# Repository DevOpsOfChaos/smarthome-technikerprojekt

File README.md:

# smarthome-technikerprojekt

Smart-Home-Grundsystem – Technikerarbeit 2026

## Projektübersicht

Eigenständig entwickeltes, lokal betriebenes Smart-Home-Grundsystem mit selbst aufgebauten Mikrocontrollergeräten, ESP-NOW-Funkkommunikation und Node-RED-Dashboard.

- **Keine Cloud** – alles läuft lokal
- **Keine Herstellerbindung** – ESP32-C3, eigene Platinen, eigene Firmware
- **Vollständig nachvollziehbar** – von der Platine bis zur Bedienoberfläche

## Architektur

```
Geräte (ESP32-C3) ──ESP-NOW──▶ Master ──MQTT──▶ Server (Raspberry Pi)
                                                 ├── Mosquitto (Broker)
                                                 ├── Node-RED (Logik + Dashboard)
                                                 └── SQLite (Persistenz)
```

## Gerätetypen

| Typ | Instanzen | Funktion |
|-----|-----------|----------|
| **net_erl** | Hall-Light, Kitchen | Relais, Umweltsensorik, Bewegung |
| **net_zrl** | Rollladen | 2-Relais-Steuerung, Kalibrierung |
| **net_sen** | Außensensor | BME280, VEML7700, Regensensor |
| **bat_sen** | Regen, Fenster | Batteriebetrieb, Deep-Sleep |

## Repository-Struktur

| Verzeichnis | Inhalt |
|-------------|--------|
| `firmware/` | **Hauptbestandteil** – PlatformIO-Projekt mit Basistypen und konkreten Geräteinstanzen |
| `hardware/` | KiCAD-Schaltpläne, Platinenlayouts, 3D-Modelle |
| `server/` | Docker-Compose-Stack (Mosquitto, Node-RED, SQLite) |
| `docs/` | Technische Dokumentation und Referenz |
| `tests/` | Testskripte und Checklisten |
| `PROTOKOLL/` | Entwicklungs- und Testprotokolle (Nachweise) |
| `esphome/` | ESPHome-Alternativlinie (nicht Bestandteil der Technikerarbeit) |

## Zwei Firmware-Linien

### Eigene Firmware (Hauptlinie)
Die eigene C++-Firmware unter `firmware/` ist der Kern des Technikerprojekts. Sie nutzt:
- **Basistyp-Architektur** – wiederverwendbare Runtime-Klassen (`NetErlRuntime`, `NetSenRuntime`, etc.)
- **ESP-NOW** – direkte Funkkommunikation zwischen Geräten und Master
- **Master-Bridge** – Übersetzung zwischen ESP-NOW und MQTT
- **Vollständige Kontrolle** – Timing, Provisionierung, Fehlerbehandlung in eigenem Code

### ESPHome-Alternative
Unter `esphome/` liegt eine alternative MQTT-Linie für Nutzer, die ESPHome oder Home Assistant bevorzugen. Diese Geräte sprechen direkt MQTT mit demselben Serververtrag. Die ESPHome-Linie ist nicht Bestandteil der Technikerarbeit, sondern eine praktische Erweiterung für Anwender.

## Quick Start

### Server starten
```bash
cd server
docker compose up -d
```
Dashboard: http://localhost:1880/ui

### Firmware bauen
```bash
cd firmware
pio run -e net_erl_hall_light -t upload
```

## Technologien

- **MCU:** ESP32-C3 (RISC-V)
- **Kommunikation:** ESP-NOW (lokal), MQTT (Server)
- **Server:** Node-RED, Mosquitto, SQLite, Docker
- **Firmware:** PlatformIO, Arduino-Framework
- **Hardware:** KiCAD, Eigenentwurf

## Lizenz

All rights reserved. Dieses Repository ist Teil einer schulischen Prüfungsleistung.  
Nach Abschluss der Prüfung behält sich der Autor einen Wechsel auf eine freizügigere Lizenz vor.

## Autor

Manuel Ries – Heinrich-Hertz-Schule Karlsruhe – Technikerarbeit 2026

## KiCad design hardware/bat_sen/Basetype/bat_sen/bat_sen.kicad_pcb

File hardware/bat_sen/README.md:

# BAT-SEN — Batteriebetriebener Sensor-Knoten (Basetype)

> `device_class: bat_sen` | `SH_CLASS_BAT_SEN (0x04)`

## Übersicht

BAT-SEN ist der Basetype für **batteriebetriebene Sensor-Knoten** mit Deep-Sleep. Optimiert für minimale Ruhestromaufnahme.

## KiCAD-Quellen

👉 **[kicad/](kicad/)** — Vollständiges KiCAD-Projekt

| Datei | Beschreibung |
|-------|-------------|
| `bat_sen.kicad_pro` | Projektdatei |
| `bat_sen.kicad_sch` | Root-Schaltplan (hierarchisch) |
| `Leistungskreis.kicad_sch` | Sub-Sheet: Power-Gating, Batterie |
| `Steuerstromkreis.kicad_sch` | Sub-Sheet: ESP32 + I²C |
| `bat_sen.kicad_pcb` | PCB-Layout (2-Lagen) |
| `Pinbelegung/Pinbelegung.txt` | GPIO-Belegung |
| `Code/SamplecodeBasis.txt` | ESP-NOW Deep-Sleep Beispiel |
| `production/` | BOM, Position, Netlist |

### SVG-Schaltpläne

- [schematics/bat_sen.svg](schematics/bat_sen.svg) — Root
- [schematics/bat_sen-Leistungskreis.svg](schematics/bat_sen-Leistungskreis.svg) — Power-Gating
- [schematics/bat_sen-Steuerstromkreis.svg](schematics/bat_sen-Steuerstromkreis.svg) — ESP32

## Stromspar-Design

- **Power-Gating:** P-MOSFET (IRF9530, SOT-23) schaltet Sensoren im Deep-Sleep ab
- **Zener-Diode:** BZX55C3V3 (DO-35) — Überspannungsschutz
- **Spannungsteiler:** R2+R5 (100K+100K) an GPIO4 — Batterieüberwachung
- **Deep-Sleep:** ~0.5–0.8 mA Board-Gesamtstrom
- **Wake-Up:** Timer (RTC) oder externer Interrupt

## Pinbelegung (Basetype)

| GPIO | Funktion | Bemerkung |
|------|----------|-----------|
| GPIO0 | I²C SDA | Optional |
| GPIO1 | I²C SCL | Optional |
| GPIO2 | Setup-Button | Lokaler Setup-/Bring-up-Taster |
| GPIO4 | V-Mess (ADC) | Batteriespannung via Spannungsteiler |
| GPIO3–10 | frei | Pinheader |
| GPIO20/21 | UART | Debug |

## Batterie-Profile

| Profil | Typ | Spannung | Kapazität |
|--------|-----|----------|-----------|
| `BAT_PROFILE_CR2032` | CR2032 | 3.0V | ~225 mAh |
| `BAT_PROFILE_2X_AA` | 2× AA | 3.0V | ~2500 mAh |
| `BAT_PROFILE_2X_AAA` | 2× AAA | 3.0V | ~1000 mAh |

## Geräte (Devices)

| Gerät | ID | Sensoren | Batterie |
|-------|-----|----------|----------|
| 👉 [bat_sen_01](devices/bat_sen_01_window_contact/) | Fensterkontakt | Reed-Schalter | 2x AAA in Serie |
| 👉 [bat_sen_02](devices/bat_sen_02_rain_sensor/) | Regensensor | ADC-Regensensor | 2× AA |

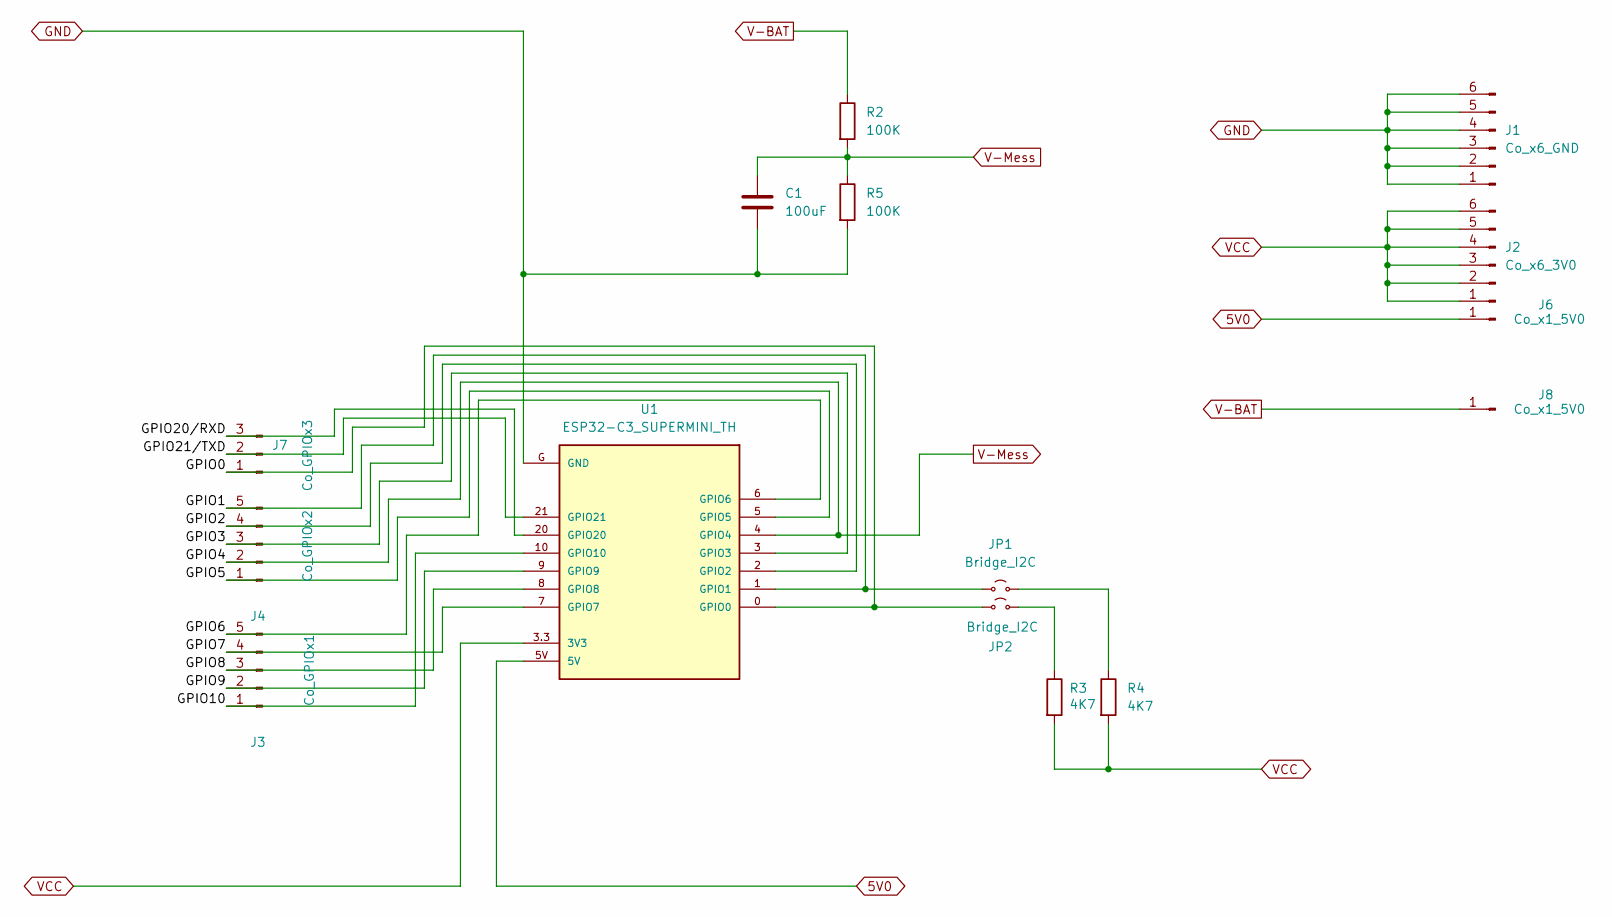
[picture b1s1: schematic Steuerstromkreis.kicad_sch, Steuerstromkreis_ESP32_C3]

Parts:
C1: 100uF; C_0603_1608Metric_Pad1.08x0.95mm_HandSolder
J1: Co_x6_GND; PinHeader_1x06_P2.54mm_Vertical
J2: Co_x6_3V0; PinHeader_1x06_P2.54mm_Vertical
J3: Co_GPIOx1; PinHeader_1x05_P2.54mm_Vertical
J4: Co_GPIOx2; PinHeader_1x05_P2.54mm_Vertical
J6, J8: Co_x1_5V0; PinHeader_1x01_P2.54mm_Vertical
J7: Co_GPIOx3; PinHeader_1x03_P2.54mm_Vertical
JP1, JP2: Bridge_I2C; SolderJumper-2_P1.3mm_Open_Pad1.0x1.5mm
R2, R5: 100K; R_0603_1608Metric_Pad0.98x0.95mm_HandSolder
R3, R4: 4K7; R_0805_2012Metric_Pad1.20x1.40mm_HandSolder
U1: ESP32-C3_SUPERMINI_TH; MODULE_ESP32-C3_SUPERMINI_TH

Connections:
5V0: J6.1, U1.5V
/Steuerstromkreis/GPIO0: J7.1, JP2.1 (A), U1.0 (GPIO0)
/Steuerstromkreis/GPIO1: J4.5, JP1.1 (A), U1.1 (GPIO1)
/Steuerstromkreis/GPIO2: J4.4, U1.2 (GPIO2)
/Steuerstromkreis/GPIO3: J4.3, U1.3 (GPIO3)
/Steuerstromkreis/GPIO5: J4.1, U1.5 (GPIO5)
/Steuerstromkreis/GPIO6: J3.5, U1.6 (GPIO6)
/Steuerstromkreis/GPIO7: J3.4, U1.7 (GPIO7)
/Steuerstromkreis/GPIO8: J3.3, U1.8 (GPIO8)
/Steuerstromkreis/GPIO9: J3.2, U1.9 (GPIO9)
/Steuerstromkreis/GPIO10: J3.1, U1.10 (GPIO10)
/Steuerstromkreis/GPIO20/RXD: J7.3, U1.20 (GPIO20)
/Steuerstromkreis/GPIO21/TXD: J7.2, U1.21 (GPIO21)
GND: C1.1, J1.1, J1.2, J1.3, J1.4, J1.5, J1.6, R5.2, U1.G (GND); also elsewhere on the board
unnamed: JP1.2 (B), R4.1
unnamed: JP2.2 (B), R3.1
V-BAT: J8.1, R2.1
V-Mess: C1.2, J4.2, R2.2, R5.1, U1.4 (GPIO4)
VCC: J2.1, J2.2, J2.3, J2.4, J2.5, J2.6, R3.2, R4.2, U1.3.3 (3V3); also elsewhere on the board

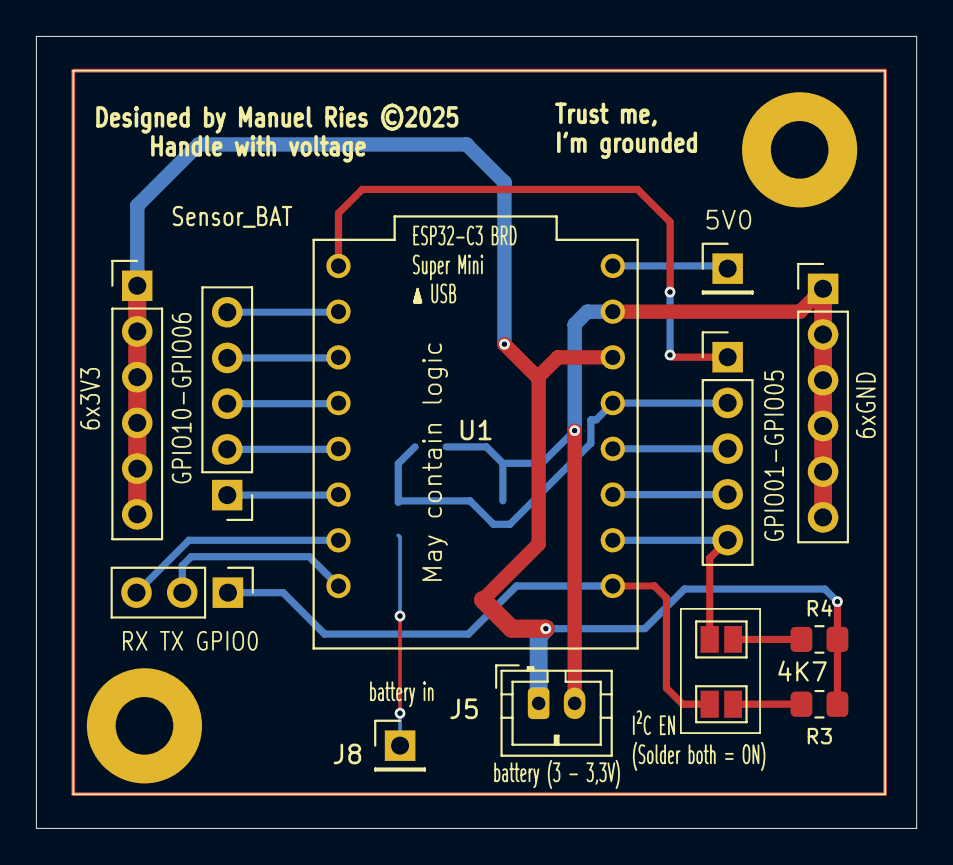
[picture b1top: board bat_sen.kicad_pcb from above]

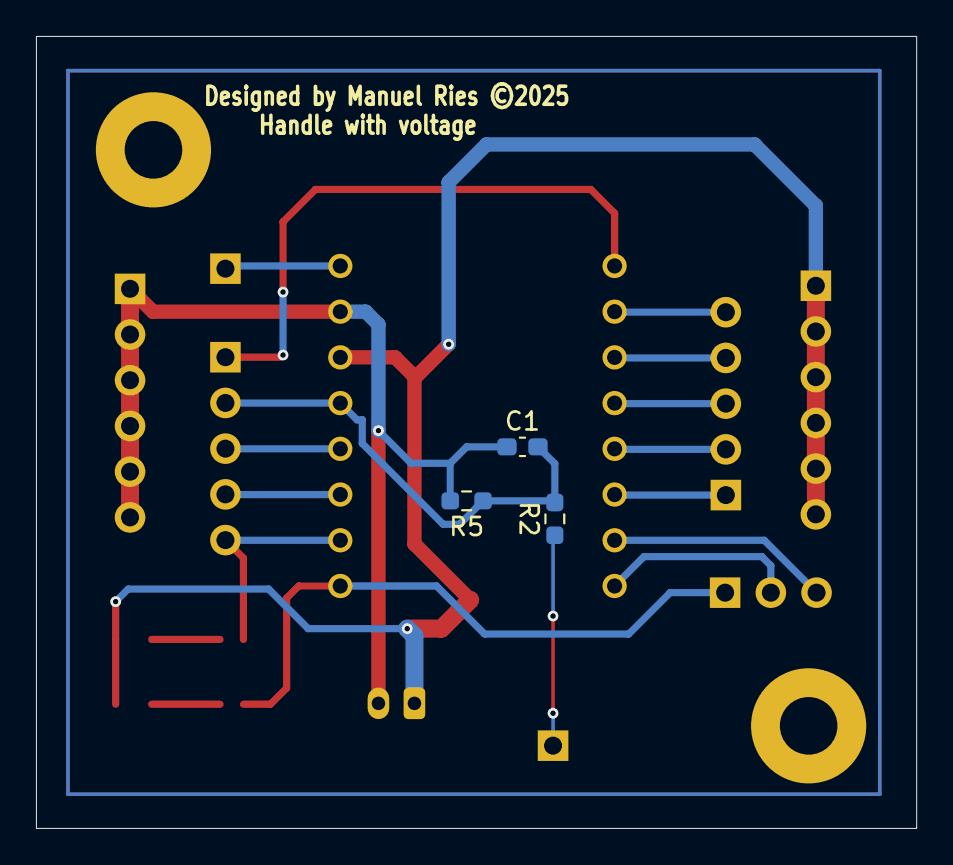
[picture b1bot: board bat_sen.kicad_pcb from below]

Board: 2 copper layers, 48.9 x 44.0 mm, 18 parts (3 on the bottom side), 19 nets.

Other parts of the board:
H1, H2: MountingHole; MountingHole_3.2mm_M3_Pad
J5: Co_x2_battery; JST_PH_B2B-PH-K_1x02_P2.00mm_Vertical

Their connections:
GND: J5.2; also elsewhere on the board
VCC: J5.1; also elsewhere on the board

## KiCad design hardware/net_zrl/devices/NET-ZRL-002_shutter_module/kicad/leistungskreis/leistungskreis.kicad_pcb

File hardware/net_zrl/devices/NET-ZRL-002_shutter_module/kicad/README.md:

# NET-ZRL-002 — KiCAD-Projekt (Geräte-Kopie)

> Kopie der Basetype-KiCAD-Dateien zur gerätespezifischen Anpassung.

## Enthaltene Platinen

| Platine | Quelle |
|---------|--------|
| [leistungskreis/](leistungskreis/) | 2-Relais-Leistungskreis (HLK-5M05, 2× HF46F, 2× IRLZ34N) |
| [steuerkreis/](steuerkreis/) | Modularer Steuerkreis (ESP32-C3, I²C, GPIOs) |

## Anpassungen für NET-ZRL-002

- [ ] 3 Taster (Hoch/Stopp/Runter) an GPIO3/4/9
- [ ] Sicherheitsschaltung: Relais-Kontakte in Serie
- [ ] Kalibrier-Fahrzeit konfigurierbar

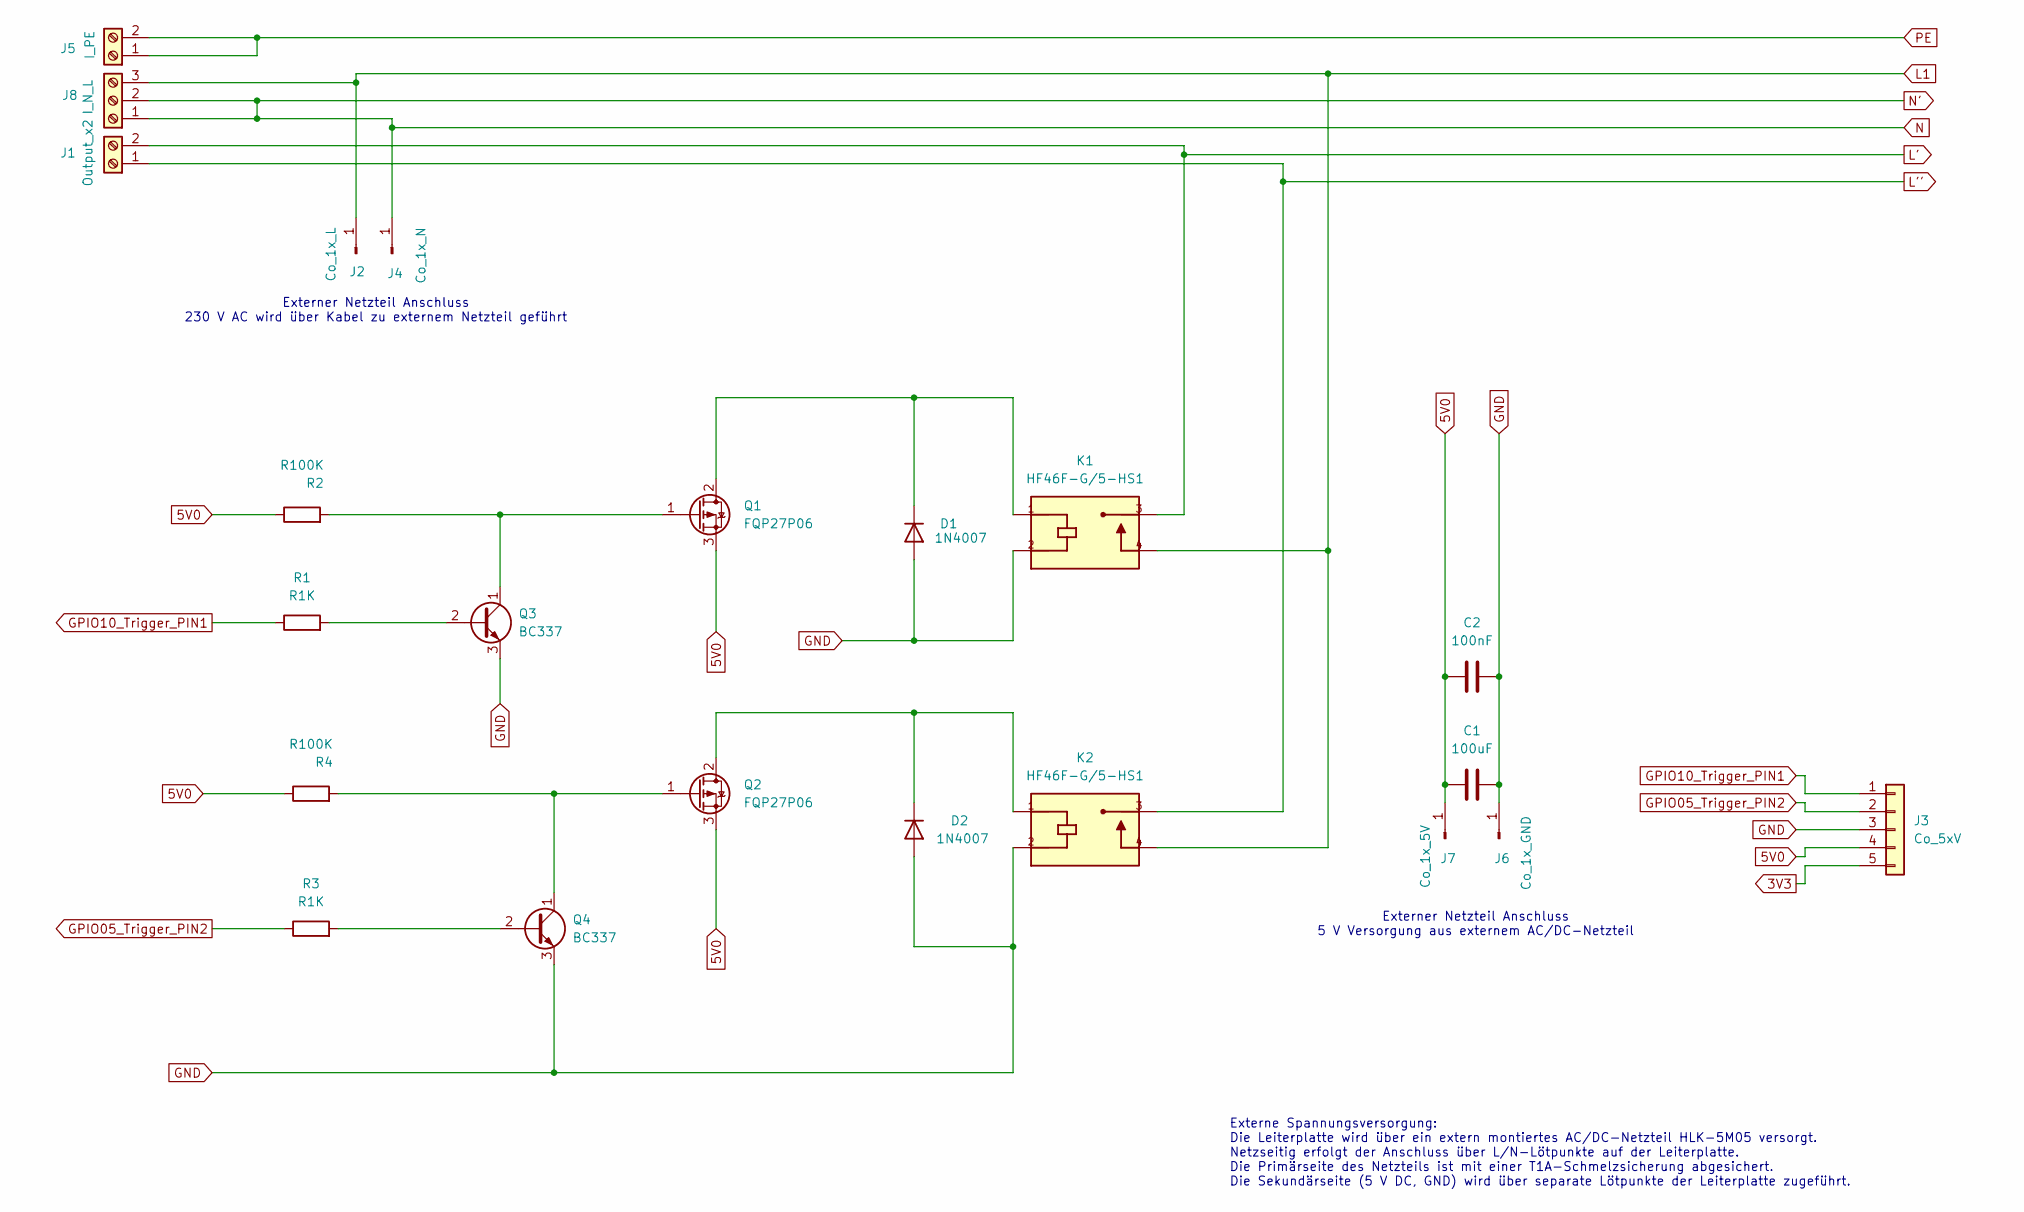
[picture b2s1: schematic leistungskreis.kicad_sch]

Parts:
C1: 100uF; CP_Elec_6.3x5.8
C2: 100nF; C_0805_2012Metric_Pad1.18x1.45mm_HandSolder
D1, D2: 1N4007; D_SOD-123
J1: Output_x2; TerminalBlock_Phoenix_MKDS-1,5-2_1x02_P5.00mm_Horizontal
J2: Co_1x_L; SolderWire-0.75sqmm_1x01_D1.25mm_OD2.3mm
J3: Co_5xV; JST_PH_B5B-PH-K_1x05_P2.00mm_Vertical
J4: Co_1x_N; SolderWire-0.75sqmm_1x01_D1.25mm_OD2.3mm
J5: I_PE; TerminalBlock_Phoenix_MKDS-1,5-2_1x02_P5.00mm_Horizontal
J6: Co_1x_GND; SolderWire-0.75sqmm_1x01_D1.25mm_OD2.3mm
J7: Co_1x_5V; SolderWire-0.75sqmm_1x01_D1.25mm_OD2.3mm
J8: I_N_L; TerminalBlock_Phoenix_MKDS-1,5-3_1x03_P5.00mm_Horizontal
K1, K2: HF46F-G/5-HS1; RELAY_HF46F_005-HS1; PARTREV 1.00
Q1, Q2: FQP27P06; TO-220-3_Vertical
Q3, Q4: BC337; TO-92_Inline
R1, R3: R1K; R_0805_2012Metric_Pad1.20x1.40mm_HandSolder
R2, R4: R100K; R_0805_2012Metric_Pad1.20x1.40mm_HandSolder

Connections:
3V3: J3.5
5V0: C1.1, C2.1, J3.4, J7.1, Q1.3 (S), Q2.3 (S), R2.1, R4.1
GND: C1.2, C2.2, D1.2 (A), D2.2 (A), J3.3, J6.1, K1.2, K2.2, Q3.3 (E), Q4.3 (E)
GPIO05_Trigger_PIN2: J3.2, R3.1
GPIO10_Trigger_PIN1: J3.1, R1.1
L1: J2.1, J8.3, K1.4, K2.4
L': J1.2, K1.3
L'': J1.1, K2.3
N: J4.1, J8.1, J8.2
unnamed: D1.1 (K), K1.1, Q1.2 (D)
unnamed: D2.1 (K), K2.1, Q2.2 (D)
unnamed: Q1.1 (G), Q3.1 (C), R2.2
unnamed: Q2.1 (G), Q4.1 (C), R4.2
unnamed: Q3.2 (B), R1.2
unnamed: Q4.2 (B), R3.2
PE: J5.1, J5.2

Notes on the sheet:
Externer Netzteil Anschluss 230 V AC wird über Kabel zu externem Netzteil geführt
Externer Netzteil Anschluss 5 V Versorgung aus externem AC/DC-Netzteil
Externe Spannungsversorgung: Die Leiterplatte wird über ein extern montiertes AC/DC-Netzteil HLK-5M05 versorgt. Netzseitig erfolgt der Anschluss über L/N-Lötpunkte auf der Leiterplatte. Die Primärseite des Netzteils ist mit einer T1A-Schmelzsicherung abgesichert. Die Sekundärseite (5 V DC, GND) wir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

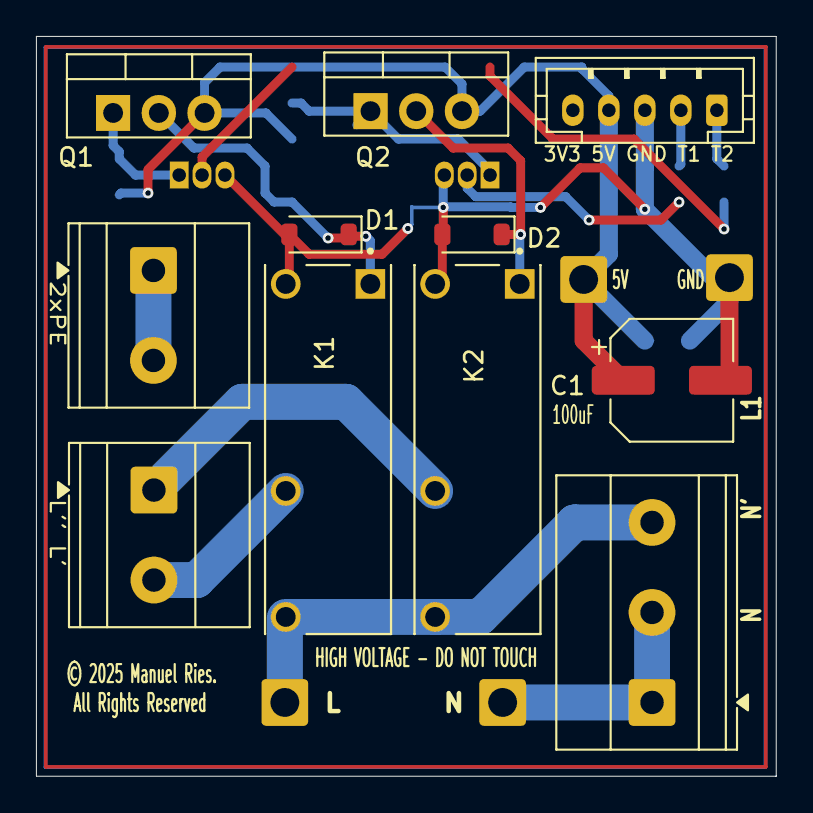
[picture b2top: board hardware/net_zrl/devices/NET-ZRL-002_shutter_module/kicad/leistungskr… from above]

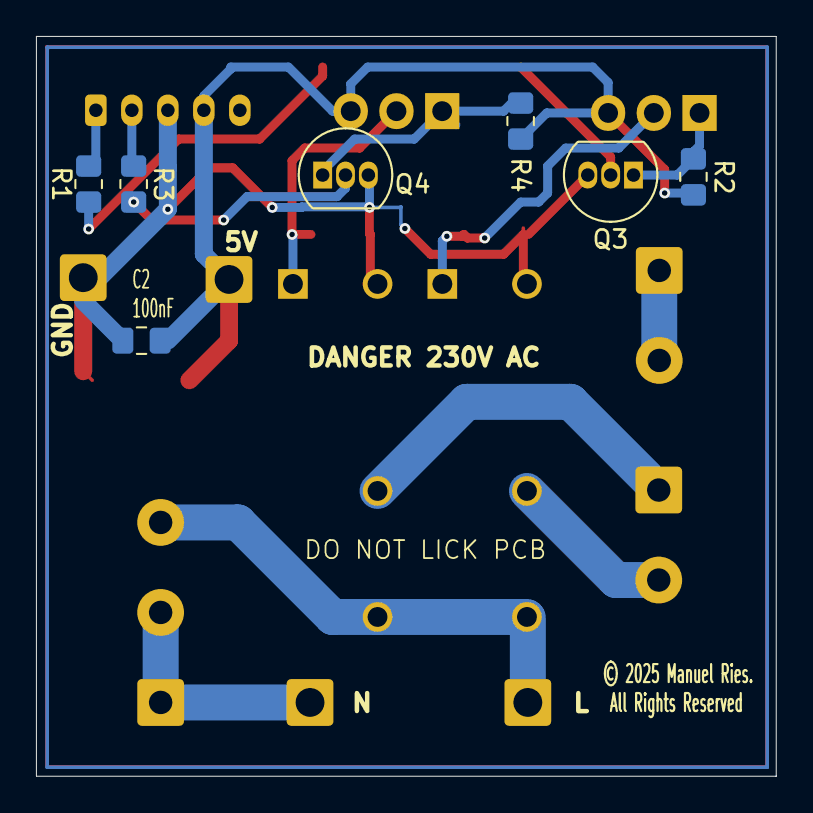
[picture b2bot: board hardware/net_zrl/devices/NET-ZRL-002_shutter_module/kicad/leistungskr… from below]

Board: 2 copper layers, 41.1 x 41.1 mm, 22 parts (7 on the bottom side), 15 nets.

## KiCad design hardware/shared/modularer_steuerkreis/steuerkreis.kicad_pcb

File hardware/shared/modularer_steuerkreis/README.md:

# Modularer Steuerkreis — KiCAD-Projekt

> Gemeinsame Steuerplatine für ALLE Relais-Knoten (`net_erl` und `net_zrl`)

## Dateien

| Datei | Beschreibung |
|-------|-------------|
| `steuerkreis.kicad_pro` | KiCAD 9.0 Projektdatei |
| `steuerkreis.kicad_sch` | Schaltplan (flat schematic) |
| `steuerkreis.kicad_pcb` | PCB-Layout (2-Lagen, 1.6mm) |
| `mod_Steuerkreis_ESP32.kicad_prl` | PCB-Regeln |
| `steuerkreis.csv` | Bauteilliste |
| `steuerkreis.step` | 3D-Modell (STEP-Export) |
| `Pinbelegung/Pinbelegung.txt` | GPIO-Belegung |
| `production/` | Fertigungsdaten (BOM, Position, Netlist) |

## Verwendung

Dieser Steuerkreis wird mit zwei verschiedenen Leistungskreisen kombiniert:

- **[net_erl](../../net_erl/leistungskreis/)** — 1-Relais-Leistungskreis
- **[net_zrl](../../net_zrl/leistungskreis/)** — 2-Relais-Leistungskreis

Die Verbindung erfolgt über ein 5-poliges JST-PH-Kabel.

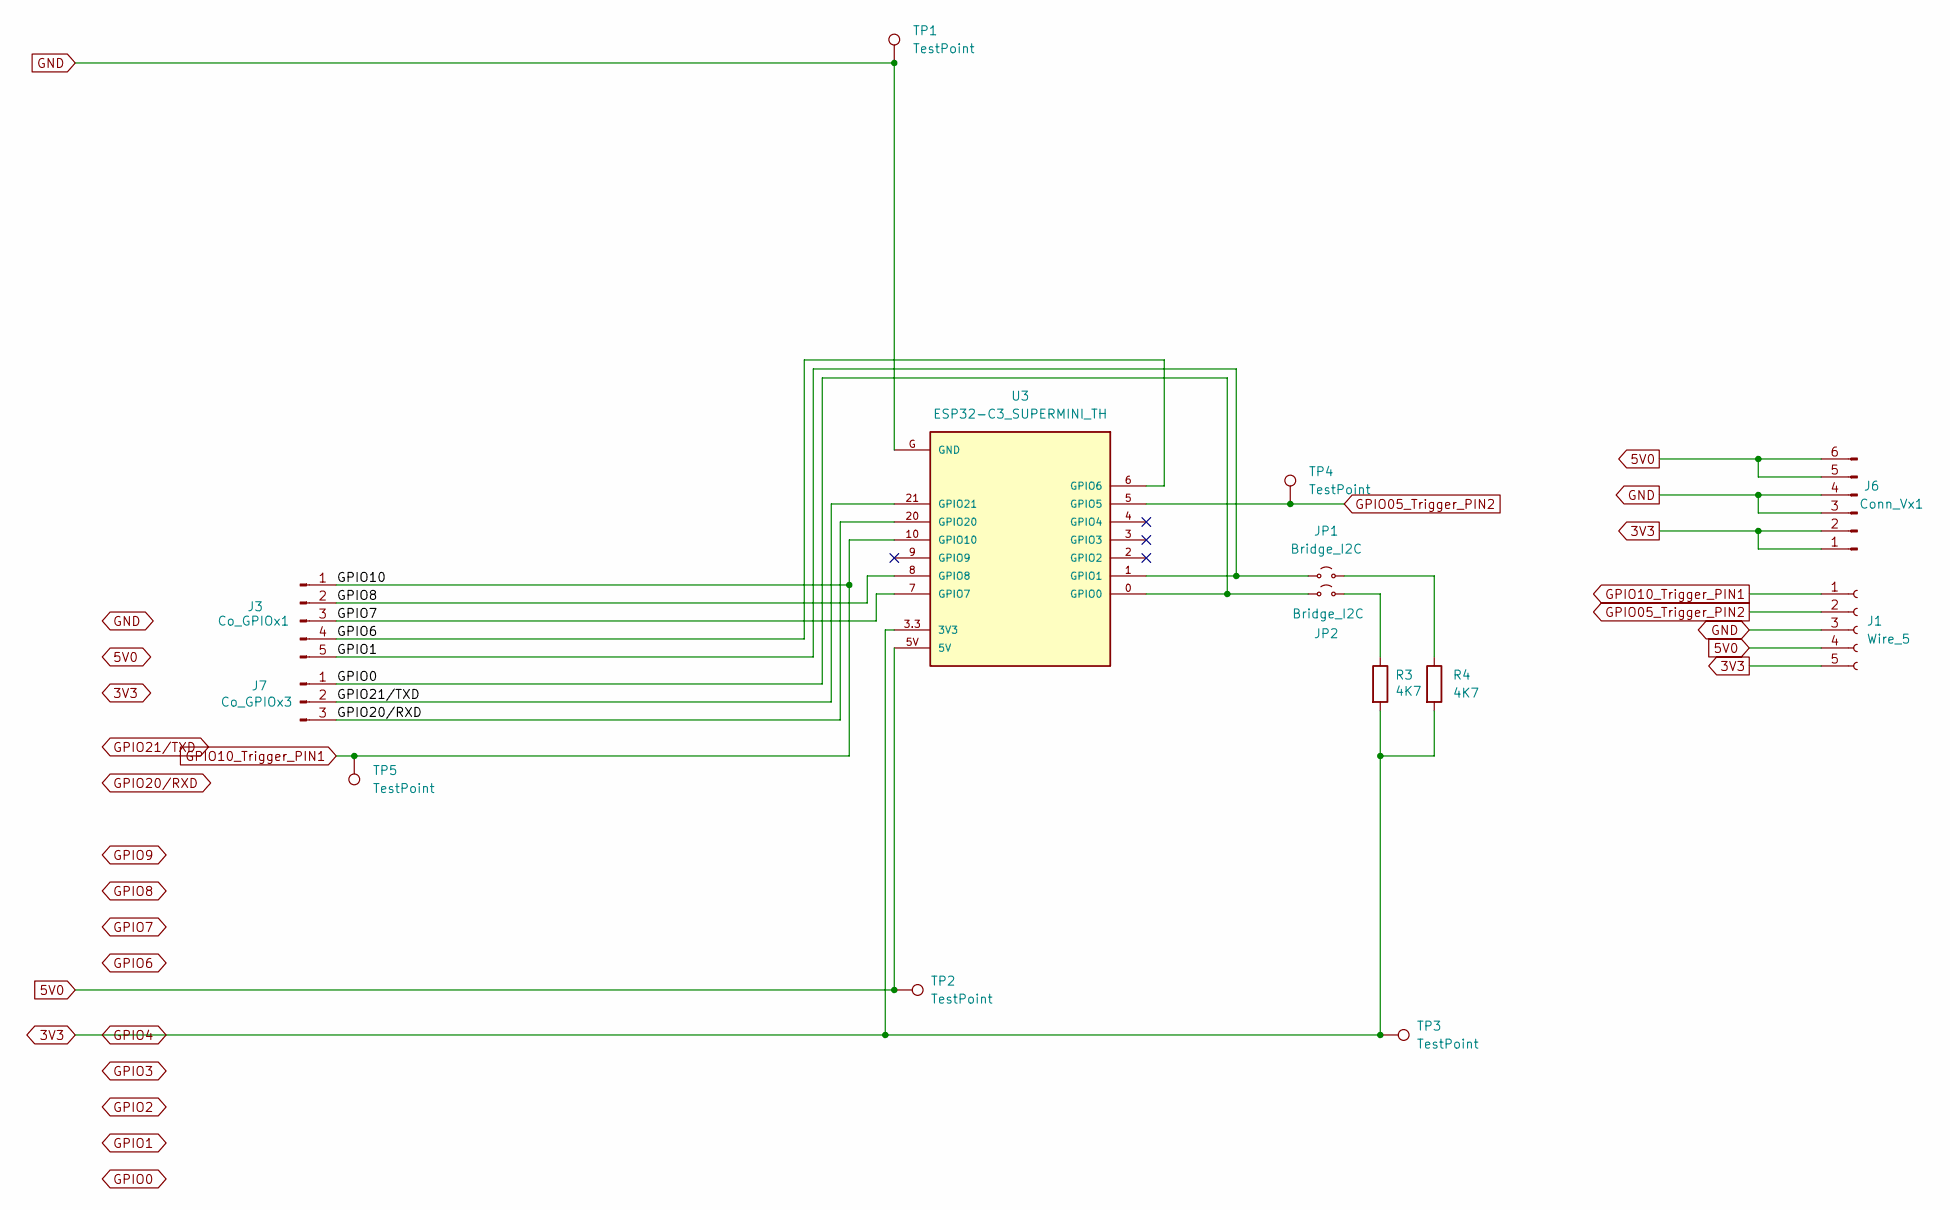
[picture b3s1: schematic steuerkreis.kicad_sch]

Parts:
J1: Wire_5; SolderWire-0.25sqmm_1x05_P4.2mm_D0.65mm_OD1.7mm
J3: Co_GPIOx1; PinHeader_1x05_P2.54mm_Vertical
J6: Conn_Vx1; PinHeader_1x06_P2.54mm_Vertical
J7: Co_GPIOx3; PinHeader_1x03_P2.54mm_Vertical
JP1, JP2: Bridge_I2C; SolderJumper-2_P1.3mm_Open_Pad1.0x1.5mm
R3, R4: 4K7; R_0805_2012Metric_Pad1.20x1.40mm_HandSolder
TP1, TP2, TP3, TP4, TP5: TestPoint; TestPoint_Pad_D1.0mm
U3: ESP32-C3_SUPERMINI_TH; MODULE_ESP32-C3_SUPERMINI_TH

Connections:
3V3: J1.5, J6.1, J6.2, R3.2, R4.2, TP3.1, U3.3.3 (3V3)
5V0: J1.4, J6.5, J6.6, TP2.1, U3.5V
/GPIO0: J7.1, JP2.1 (A), U3.0 (GPIO0)
/GPIO1: J3.5, JP1.1 (A), U3.1 (GPIO1)
/GPIO6: J3.4, U3.6 (GPIO6)
/GPIO7: J3.3, U3.7 (GPIO7)
/GPIO8: J3.2, U3.8 (GPIO8)
/GPIO20/RXD: J7.3, U3.20 (GPIO20)
/GPIO21/TXD: J7.2, U3.21 (GPIO21)
GND: J1.3, J6.3, J6.4, TP1.1, U3.G (GND)
GPIO05_Trigger_PIN2: J1.2, TP4.1, U3.5 (GPIO5)
GPIO10_Trigger_PIN1: J1.1, J3.1, TP5.1, U3.10 (GPIO10)
unnamed: JP1.2 (B), R4.1
unnamed: JP2.2 (B), R3.1

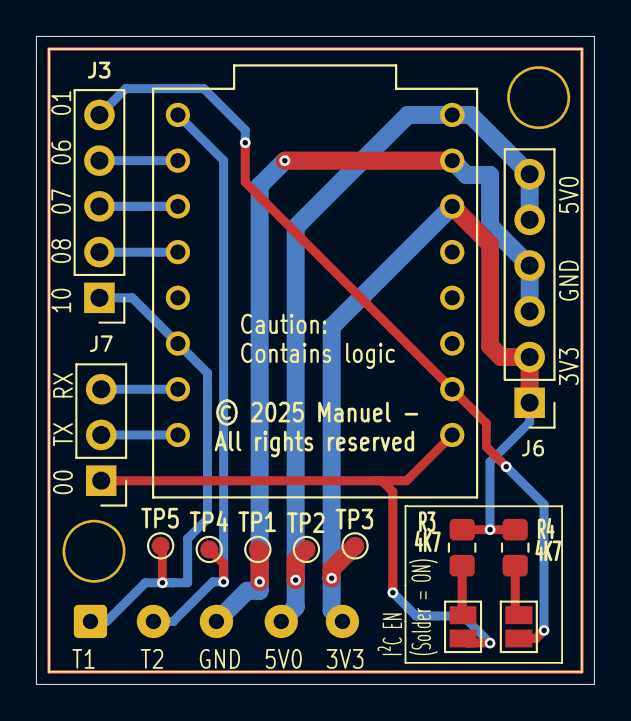
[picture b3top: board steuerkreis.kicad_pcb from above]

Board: 2 copper layers, 31.0 x 36.0 mm, 16 parts (0 on the bottom side), 14 nets.

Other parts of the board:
MH: Mounting_Hole_M3
MH#2: Mounting_Hole_M3

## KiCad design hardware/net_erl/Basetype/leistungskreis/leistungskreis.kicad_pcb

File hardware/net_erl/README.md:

# NET-ERL — 1-Relais-Knoten (Basetype)

> `device_class: net_erl` | `SH_CLASS_NET_ERL (0x01)`

## Übersicht

NET-ERL ist der Basetype für **netzbetriebene 1-Relais-Knoten**. Einsatz: Lampen, Steckdosen, Flurlicht-Steuerung.

## KiCAD-Quellen

| Platine | Pfad | Typ |
|---------|------|-----|
| 🔑 Modularer Steuerkreis | [../shared/modularer_steuerkreis/](../shared/modularer_steuerkreis/) | Gemeinsam mit net_zrl |
| ⚡ Leistungskreis (230V) | [leistungskreis/](leistungskreis/) | NET-ERL-spezifisch |
| 🔬 Simulation | [simulation/](simulation/) | LTSpice |

### Leistungskreis

👉 **[leistungskreis_1relais.md](leistungskreis_1relais.md)** — Vollständige Doku mit BOM und Schaltungsdesign

→ KiCAD: `Leistungskreis_1Relai_korrektur.{kicad_pro,sch,pcb}` im Ordner [leistungskreis/](leistungskreis/)

→ SVG-Schaltplan: [schematics/leistungskreis.svg](schematics/leistungskreis.svg)

### Steuerkreis

Der Steuerkreis ist **identisch** mit dem von net_zrl:

👉 **[../shared/modularer_steuerkreis.md](../shared/modularer_steuerkreis.md)** — Vollständige Doku

→ KiCAD: [../shared/modularer_steuerkreis/](../shared/modularer_steuerkreis/)

→ SVG: [../shared/schematics/steuerkreis.svg](../shared/schematics/steuerkreis.svg)

## Pinbelegung (Basetype)

| GPIO | Funktion | Bemerkung |
|------|----------|-----------|
| GPIO0 | I²C SDA | Sensoren (optional) |
| GPIO1 | I²C SCL | Sensoren (optional) |
| GPIO5 | Trigger_PIN2 | NC bei 1-Relais |
| GPIO10 | Trigger_PIN1 | Relais (via PC817) |
| GPIO20 | RX | UART Debug |
| GPIO21 | TX | UART Debug |

## Geräte (Devices)

| Gerät | ID | Sensoren |
|-------|-----|----------|
| 👉 [NET-ERL-001](devices/NET-ERL-001_hall_module/) | Flurmodul Basis | BME280, VEML7700, PIR |
| 👉 [NET-ERL-002](devices/NET-ERL-002_hall_module_led_ring/) | Flurmodul LED-Ring | BME680, VEML7700, ENS160, LD2410, NeoPixel |

→ Jedes Gerät hat eigene GPIO-Belegung und Sensor-Konfiguration. Siehe jeweiligen Device-Ordner.

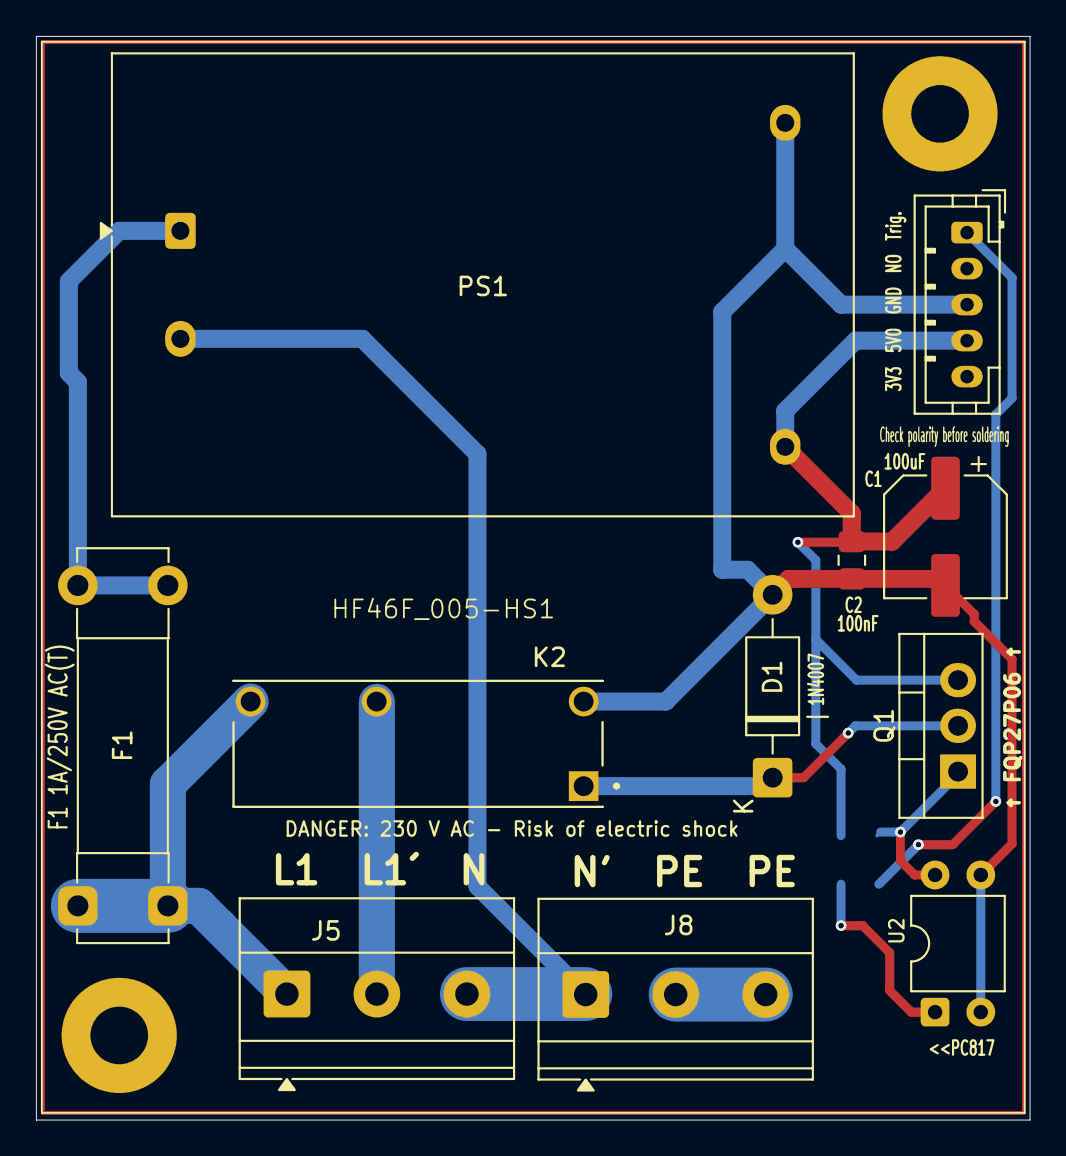
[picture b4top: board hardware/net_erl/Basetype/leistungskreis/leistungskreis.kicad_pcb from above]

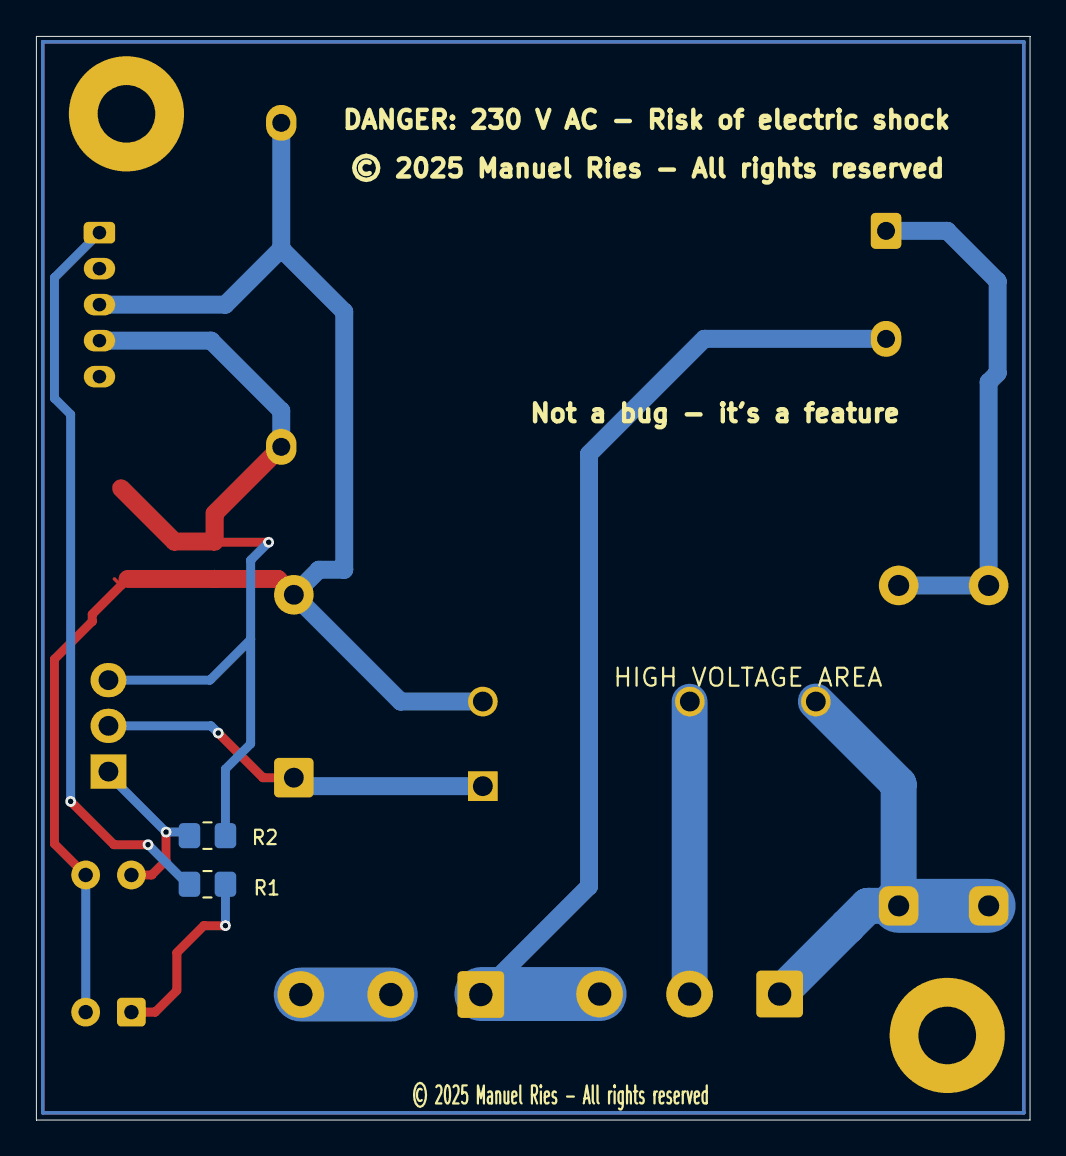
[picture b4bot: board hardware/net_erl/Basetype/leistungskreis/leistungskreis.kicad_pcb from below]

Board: 2 copper layers, 55.2 x 60.2 mm, 15 parts (2 on the bottom side), 11 nets.

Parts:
C1: 100uF; CP_Elec_6.3x5.8
C2: 100nF; C_0805_2012Metric_Pad1.18x1.45mm_HandSolder
D1: 1N4007; D_DO-41_SOD81_P10.16mm_Horizontal
F1: Fuse; Fuseholder_Clip-5x20mm_Bel_FC-203-22_Lateral_P17.80x5.00mm_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
H1, H2: MountingHole; MountingHole_3.2mm_M3_Pad
J1: Co_5xV; JST_PH_B5B-PH-K_1x05_P2.00mm_Vertical
J5: Co_x3; TerminalBlock_Phoenix_MKDS-1,5-3_1x03_P5.00mm_Horizontal
J8: Co_x31; TerminalBlock_Phoenix_MKDS-1,5-3_1x03_P5.00mm_Horizontal
K2: HF46F_005-HS1; RELAY_HF46F_005-HS1
PS1: HLK-5M05; Converter_ACDC_Hi-Link_HLK-5Mxx
Q1: FQP27P06; TO-220-3_Vertical
R1: R330; R_0805_2012Metric_Pad1.20x1.40mm_HandSolder
R2: R100K; R_0805_2012Metric_Pad1.20x1.40mm_HandSolder
U2: PC817; DIP-4_W7.62mm

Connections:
5V0: C1.1, C2.1, J1.4, PS1.4 (+Vout), Q1.3 (S), R2.1
GND: C1.2, C2.2, D1.2 (A), J1.3, K2.2, PS1.3 (-Vout), U2.2, U2.3
GPIO10_Trigger_PIN1: J1.1, R1.1
L1 230VAC: F1.1, J5.1, K2.4
N: J5.3, J8.1, PS1.2 (AC/N)
unnamed: D1.1 (K), K2.1, Q1.2 (D)
unnamed: J5.2, K2.3
unnamed: F1.2, PS1.1 (AC/L)
unnamed: Q1.1 (G), R2.2, U2.4
unnamed: R1.2, U2.1
PE: J8.2, J8.3

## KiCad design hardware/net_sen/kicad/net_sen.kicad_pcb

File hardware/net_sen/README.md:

# NET-SEN — Netzbetriebener Sensor-Knoten (Basetype)

> `device_class: net_sen` | `SH_CLASS_NET_SEN (0x03)`

## Übersicht

NET-SEN ist der Basetype für **dauerhaft netzbetriebene Sensor-Knoten**. Kein Sleep — immer online.

## KiCAD-Quellen

👉 **[kicad/](kicad/)** — Vollständiges KiCAD-Projekt

| Datei | Beschreibung |
|-------|-------------|
| `net_sen.kicad_pro` | Projektdatei |
| `net_sen.kicad_sch` | Root-Schaltplan (hierarchisch) |
| `Leistungskreis.kicad_sch` | Sub-Sheet: 230V-Netzteil |
| `Steuerstromkreis.kicad_sch` | Sub-Sheet: ESP32 + I²C |
| `net_sen.kicad_pcb` | PCB-Layout (2-Lagen) |
| `Bilder/` | Layout-Ansichten (7 PNGs) |
| `production/` | BOM, Position, Netlist |

### SVG-Schaltpläne

- [schematics/net_sen.svg](schematics/net_sen.svg) — Root
- [schematics/net_sen-Leistungskreis.svg](schematics/net_sen-Leistungskreis.svg) — Netzteil
- [schematics/net_sen-Steuerstromkreis.svg](schematics/net_sen-Steuerstromkreis.svg) — ESP32

## Platinen-Design

Einteiliger Aufbau (nicht modular):

- **HLK-PM03:** 230V AC → 3.3V DC
- **Feinsicherung:** 5×20mm
- **I²C:** GPIO0/1 mit 4K7 Pullups (Lötbrücken)
- **230V-Eingang:** Phoenix MKDS 1.5/3

## Pinbelegung (Basetype)

| GPIO | Funktion |
|------|----------|
| GPIO0 | I²C SDA |
| GPIO1 | I²C SCL |
| GPIO2–10 | frei (Pinheader) |
| GPIO20/21 | UART |

## Versionen

1. **Standard Version** (aktiv) — im Ordner [kicad/](kicad/)
2. **Version mit TCA9548APWR** — Mit I²C-Multiplexer (separater KiCAD-Ordner)

## Geräte (Devices)

| Gerät | ID | Sensoren |
|-------|-----|----------|
| 👉 [NET-SEN-002](devices/NET-SEN-002_weather_station/) | Wetterstation | BME280, VEML7700, Regensensor |

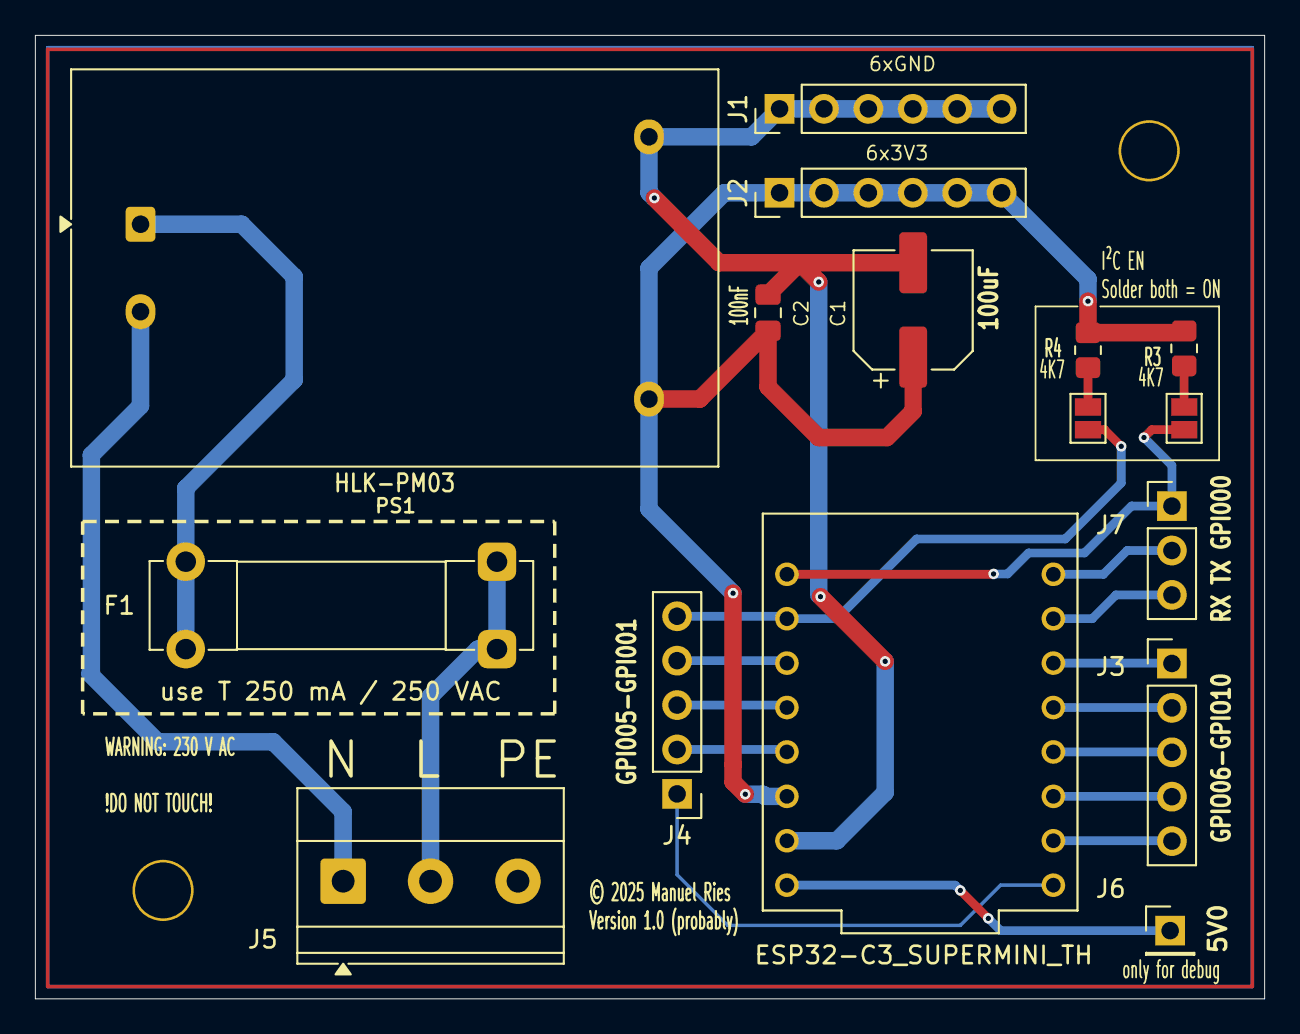
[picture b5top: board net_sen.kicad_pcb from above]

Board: 2 copper layers, 70.3 x 55.1 mm, 18 parts (0 on the bottom side), 21 nets.

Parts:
C1: 100uF; CP_Elec_6.3x5.8
C2: 100nF; C_0805_2012Metric_Pad1.18x1.45mm_HandSolder
ESP32-C3_SUPERMINI_TH: ESP32-C3_SUPERMINI_TH; MODULE_ESP32-C3_SUPERMINI_TH
F1: Fuse; Fuseholder_Clip-5x20mm_Bel_FC-203-22_Lateral_P17.80x5.00mm_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
H1, H2: MountingHole; Mounting_Hole_M3
J1: Co_x6_GND; PinHeader_1x06_P2.54mm_Vertical
J2: Co_x6_3V3; PinHeader_1x06_P2.54mm_Vertical
J3: Co_GPIOx1; PinHeader_1x05_P2.54mm_Vertical
J4: Co_GPIOx2; PinHeader_1x05_P2.54mm_Vertical
J5: Input_x3; TerminalBlock_Phoenix_MKDS-1,5-3_1x03_P5.00mm_Horizontal
J6: Co_x1_5V0; PinHeader_1x01_P2.54mm_Vertical
J7: Co_GPIOx3; PinHeader_1x03_P2.54mm_Vertical
JP1, JP2: Bridge_I2C; SolderJumper-2_P1.3mm_Open_Pad1.0x1.5mm
PS1: HLK-PM03; Converter_ACDC_Hi-Link_HLK-PMxx
R3, R4: 4K7; R_0805_2012Metric_Pad1.20x1.40mm_HandSolder

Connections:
3V3: C1.1, C2.2, ESP32-C3_SUPERMINI_TH.3.3 (3V3), J2.1, J2.2, J2.3, J2.4, J2.5, J2.6, PS1.4 (+Vout), R3.2, R4.2
5V0: ESP32-C3_SUPERMINI_TH.5V, J6.1
/Steuerstromkreis/GPIO0: ESP32-C3_SUPERMINI_TH.0 (GPIO0), J7.1, JP2.1 (A)
/Steuerstromkreis/GPIO1: ESP32-C3_SUPERMINI_TH.1 (GPIO1), J4.5, JP1.1 (A)
/Steuerstromkreis/GPIO2: ESP32-C3_SUPERMINI_TH.2 (GPIO2), J4.4
/Steuerstromkreis/GPIO3: ESP32-C3_SUPERMINI_TH.3 (GPIO3), J4.3
/Steuerstromkreis/GPIO4: ESP32-C3_SUPERMINI_TH.4 (GPIO4), J4.2
/Steuerstromkreis/GPIO5: ESP32-C3_SUPERMINI_TH.5 (GPIO5), J4.1
/Steuerstromkreis/GPIO6: ESP32-C3_SUPERMINI_TH.6 (GPIO6), J3.5
/Steuerstromkreis/GPIO7: ESP32-C3_SUPERMINI_TH.7 (GPIO7), J3.4
/Steuerstromkreis/GPIO8: ESP32-C3_SUPERMINI_TH.8 (GPIO8), J3.3
/Steuerstromkreis/GPIO9: ESP32-C3_SUPERMINI_TH.9 (GPIO9), J3.2
/Steuerstromkreis/GPIO10: ESP32-C3_SUPERMINI_TH.10 (GPIO10), J3.1
/Steuerstromkreis/GPIO20/RXD: ESP32-C3_SUPERMINI_TH.20 (GPIO20), J7.3
/Steuerstromkreis/GPIO21/TXD: ESP32-C3_SUPERMINI_TH.21 (GPIO21), J7.2
GND: C1.2, C2.1, ESP32-C3_SUPERMINI_TH.G (GND), J1.1, J1.2, J1.3, J1.4, J1.5, J1.6, PS1.3 (-Vout)
L1 230VAC: F1.1, J5.2
N: J5.1, PS1.2 (AC/N)
unnamed: JP1.2 (B), R4.1
unnamed: JP2.2 (B), R3.1
unnamed: F1.2, PS1.1 (AC/L)

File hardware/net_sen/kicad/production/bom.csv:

Designator,Footprint,Quantity,Value,LCSC Part #
C1,CP_Elec_6.3x5.8,1,100uF,
C2,0805,1,100nF,
ESP32-C3_SUPERMINI_TH,MODULE_ESP32-C3_SUPERMINI_TH,1,ESP32-C3_SUPERMINI_TH,
F1,Fuseholder_Clip-5x20mm_Bel_FC-203-22_Lateral_P17.80x5.00mm_D1.17mm_Horizontal,1,Fuse,
J1,PinHeader_1x06_P2.54mm_Vertical,1,Co_x6_GND,
J2,PinHeader_1x06_P2.54mm_Vertical,1,Co_x6_3V3,
J3,PinHeader_1x05_P2.54mm_Vertical,1,Co_GPIOx1,
J4,PinHeader_1x05_P2.54mm_Vertical,1,Co_GPIOx2,
J5,"TerminalBlock_Phoenix_MKDS-1,5-3_1x03_P5.00mm_Horizontal",1,Input_x3,
J6,PinHeader_1x01_P2.54mm_Vertical,1,Co_x1_5V0,
J7,PinHeader_1x03_P2.54mm_Vertical,1,Co_GPIOx3,
"JP1, JP2",SolderJumper-2_P1.3mm_Open_Pad1.0x1.5mm,2,Bridge_I2C,
PS1,Converter_ACDC_Hi-Link_HLK-PMxx,1,HLK-PM03,
"R3, R4",0805,2,4K7,

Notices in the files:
hardware/bat_sen/Basetype/bat_sen/bat_sen.kicad_pcb:
Designed by Manuel Ries ©2025
hardware/net_erl/Basetype/leistungskreis/leistungskreis.kicad_pcb:
© 2025 Manuel Ries - All rights reserved
hardware/shared/modularer_steuerkreis/steuerkreis.kicad_pcb:
© 2025 Manuel -
